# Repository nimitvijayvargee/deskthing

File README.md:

# deskthing
Spotify car thing made for your desk!

This project uses a Raspberry Pi Pico W and some cheap components, which puts the components cost just around $10. It acts as an interface for your spotify playback, allowing you to change tracks, fast forward, pause or play from a single input knob. The design is based on the spotify car thing and a tiny FM radio look. The main assembly comprises of 4 screws, ssome basic assembly and 3 3D printed case parts. It is intended to be a quick, practical project that helps me keep my phone away; since I can do any music stuff on this device.

# BOM
|Item       |Link                                                                    |Cost|
|-----------|------------------------------------------------------------------------|----|
|PCB        |https://lioncircuits.com/                                               |13  |
|Pico W     |https://robocraze.com/products/raspberry-pi-pico-w/                     |10  |
|LCD ST7735R|https://www.ktron.in/product/1-8-inch-tft-lcd-display-128x160-non-touch/|5   |
|Case       |Print Legion                                                            |    |
|EC11-20mm  |https://amzn.in/d/0mwhJB2                                               |4   |
|M3 Screws  |[already have]                                                          |    |
|Total      |                                                                        |32  |

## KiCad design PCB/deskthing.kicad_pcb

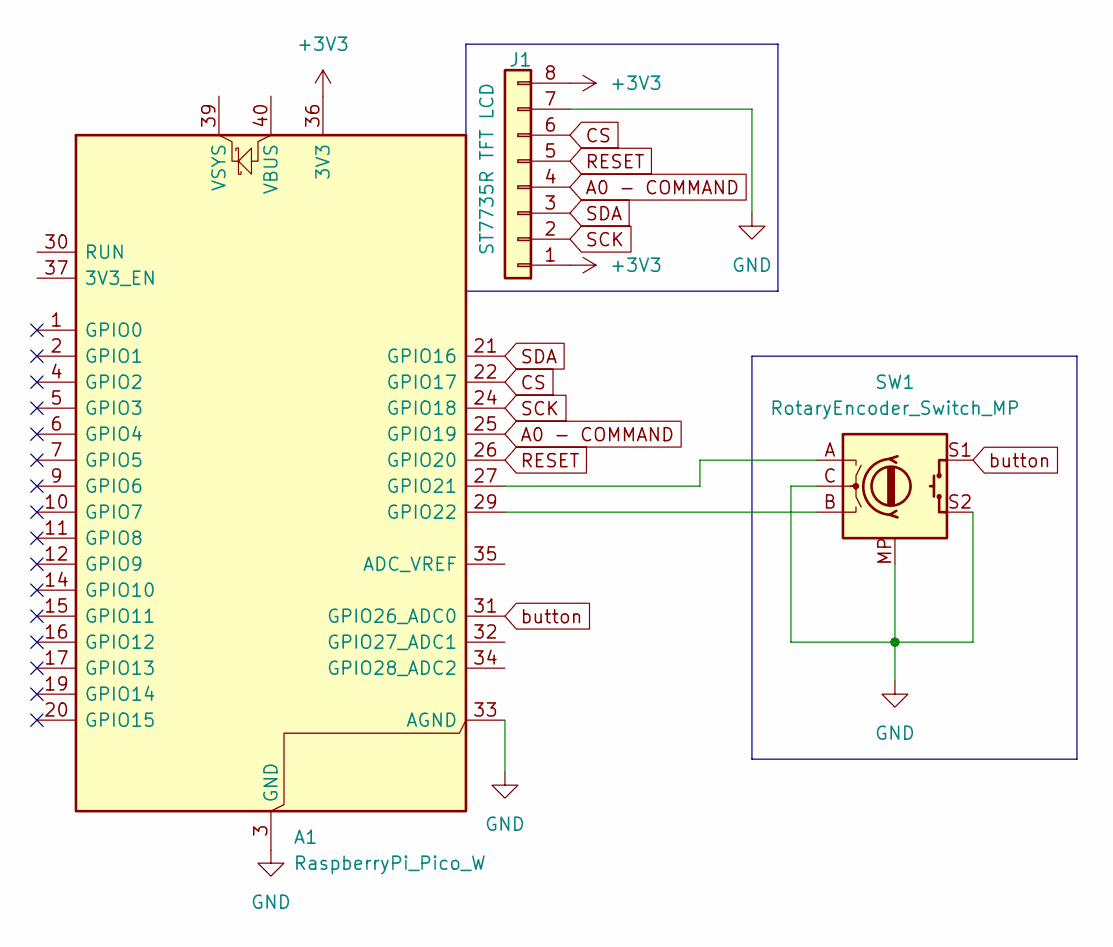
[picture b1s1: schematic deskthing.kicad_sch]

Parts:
A1: RaspberryPi_Pico_W; RaspberryPi_Pico_Common_THT
J1: ST7735R TFT LCD; PinHeader_1x08_P2.54mm_Vertical
SW1: RotaryEncoder_Switch_MP; RotaryEncoder_Alps_EC11E-Switch_Vertical_H20mm_MountingHoles

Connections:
+3V3: A1.36 (3V3), J1.1, J1.8
A0 - COMMAND: A1.25 (GPIO19), J1.4
CS: A1.22 (GPIO17), J1.6
GND: A1.3 (GND), A1.8 (GND), A1.13 (GND), A1.18 (GND), A1.23 (GND), A1.28 (GND), A1.33 (AGND), A1.38 (GND), J1.7, SW1.C, SW1.MP, SW1.S2
unnamed: A1.27 (GPIO21), SW1.A
unnamed: A1.29 (GPIO22), SW1.B
RESET: A1.26 (GPIO20), J1.5
SCK: A1.24 (GPIO18), J1.2
SDA: A1.21 (GPIO16), J1.3
button: A1.31 (GPIO26_ADC0), SW1.S1

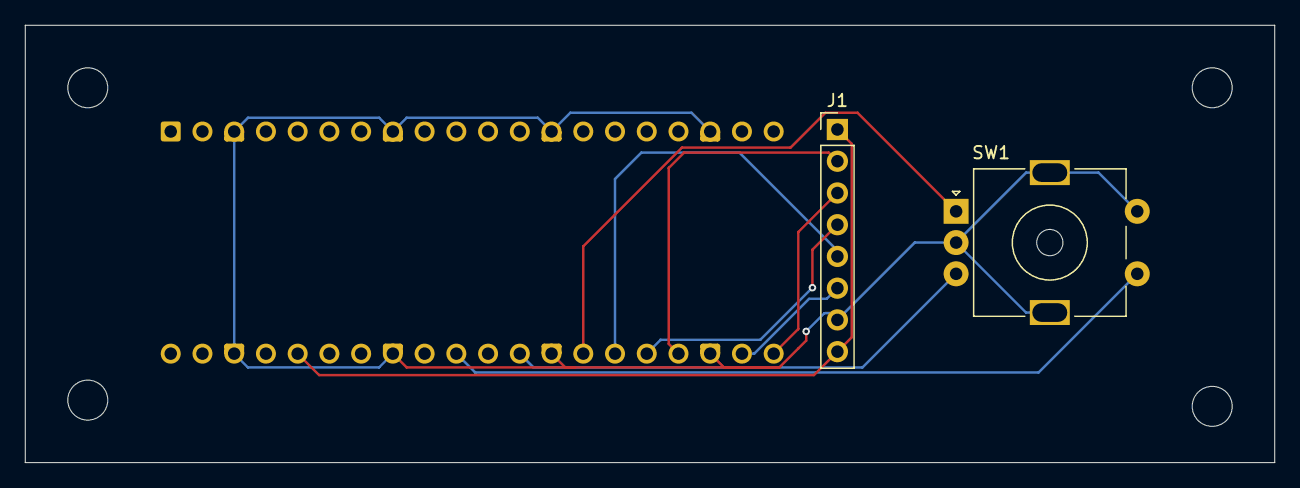
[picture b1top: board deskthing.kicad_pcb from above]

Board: 2 copper layers, 100.0 x 35.0 mm, 3 parts (1 on the bottom side), 10 nets.

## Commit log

2025-07-31 Add BOM
2025-07-31 Added PCB and assembly cuz i forgot lol
2025-07-31 Fix bom hate excel
2025-08-04 Ready for rereview round 2
